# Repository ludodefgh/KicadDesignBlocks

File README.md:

# KicadDesignBlocks

Reusable KiCad circuit blocks: a schematic and its PCB layout, one self-contained
KiCad project per folder. Each project can be opened or shared on its own, for
example for an external review.

| Block | What it is | Status |
|---|---|---|
| [`TPS563201/`](TPS563201/) | Buck 5 V → 3.3 V / 1 A, TI TPS563201, 4 layers. Generated from the MultiSensors board (private repository) | layout done, not fabricated |
| [`TPS5430Buck/`](TPS5430Buck/) | Power input + buck based on the TI TPS5430: screw-terminal input, polyfuses (schematic note: "5/12/24V Power In") | earlier stand-alone project, history imported from the former `TPS5430Buck` repo |

## Conventions

- One folder per block, named after the main part, holding its own `.kicad_pro`.
- Symbols that are not in the standard KiCad libraries go in a project-local library
  (`sym/`, declared in the folder's `sym-lib-table`), so the project opens anywhere.
- `docs/` holds what a reviewer needs without KiCad: schematic PDF, layout image, and
  the sources the values came from.
- If a block is generated from another project, its README says so and names the
  script. Change it at the source and re-export.

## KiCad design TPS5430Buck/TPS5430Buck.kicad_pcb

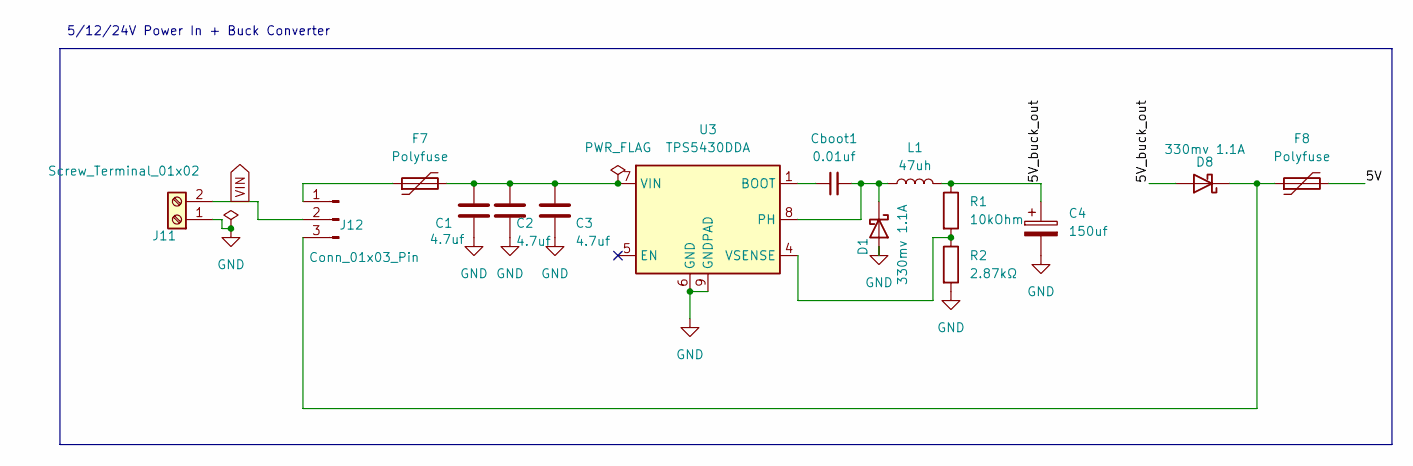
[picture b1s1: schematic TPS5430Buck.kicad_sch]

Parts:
C1, C2, C3: 4.7uf; C_1206_3216Metric; LCSC C29823
C4: 150uf; CP_EIA-7343-31_Kemet-D; LCSC C1953305
Cboot1: 0.01uf; R_0805_2012Metric; LCSC C1710
D1, D8: 330mv 1.1A; D_SMA; LCSC C8678
F7: Polyfuse; Fuse_1206_3216Metric; LCSC C7542958
F8: Polyfuse; Fuse_1206_3216Metric; LCSC C883127
J11: Screw_Terminal_01x02; TerminalBlock_Ningbo-Kagnex_HB9500M_1x02_P9.5mm; lcsc C601239
J12: Conn_01x03_Pin; PinHeader_1x03_P2.54mm_Vertical
L1: 47uh; L_7.3x7.3_H4.5; LCSC C168137
R1: 10kOhm; R_0201_0603Metric; LCSC C106225
R2: 2.87kΩ; R_0402_1005Metric; LCSC C334673
U3: TPS5430DDA; TI_SO-PowerPAD-8_ThermalVias; LCSC C9864

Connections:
/5V: F8.2
/5V_buck_out: C4.1, D8.2 (A), L1.2, R1.1
GND: C1.2, C2.2, C3.2, C4.2, D1.2 (A), J11.1, R2.2, U3.6 (GND), U3.9 (GNDPAD)
unnamed: Cboot1.2, D1.1 (K), L1.1, U3.8 (PH)
unnamed: D8.1 (K), F8.1, J12.3
unnamed: F7.1, J12.1
unnamed: Cboot1.1, U3.1 (BOOT)
unnamed: C1.1, C2.1, C3.1, F7.2, U3.7 (VIN)
unnamed: R1.2, R2.1, U3.4 (VSENSE)
VIN: J11.2, J12.2

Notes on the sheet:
5/12/24V Power In + Buck Converter

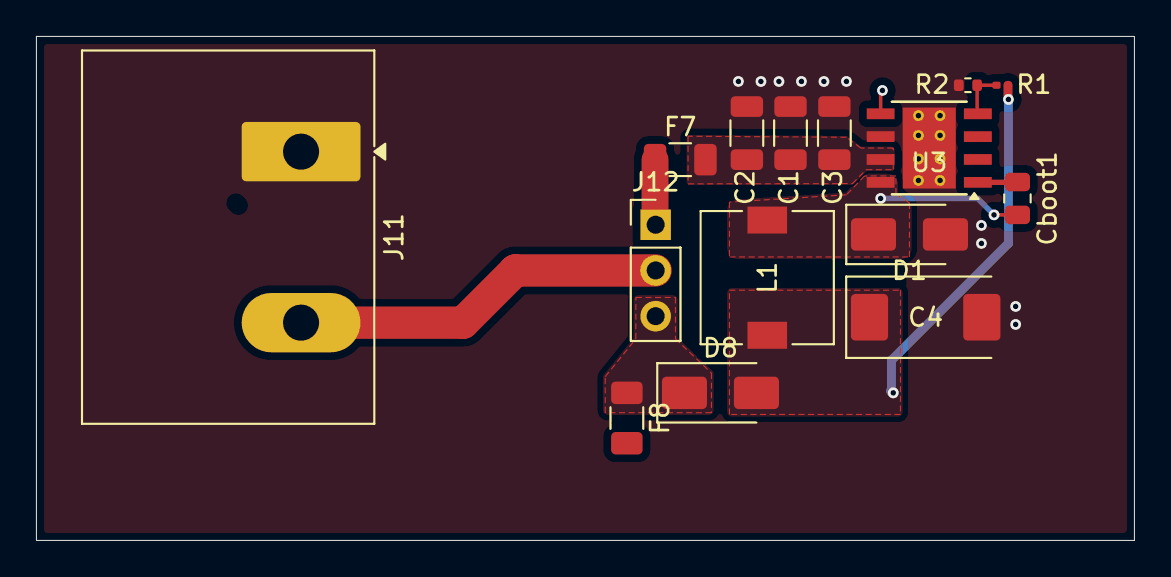
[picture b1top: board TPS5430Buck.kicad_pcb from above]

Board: 2 copper layers, 61.0 x 28.0 mm, 15 parts (0 on the bottom side), 9 nets.

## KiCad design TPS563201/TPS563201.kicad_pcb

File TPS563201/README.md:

# TPS563201 buck block: 5 V → 3.3 V / 1 A

A self-contained KiCad 10 project with just the TPS563201 and its passives, as laid
out in the MultiSensors sensor node (a private repository). It
exists so the power stage can be reviewed on its own, without the rest of the board.

| File | What it is |
|---|---|
| `TPS563201.kicad_pro` / `.kicad_sch` / `.kicad_pcb` | the project (open the `.kicad_pro`) |
| `docs/TPS563201-schematic.pdf` | schematic, readable without KiCad |
| `docs/TPS563201-layout.svg` | F.Cu, B.Cu, silkscreen and outline, readable without KiCad |
| `docs/webench/` | TI WEBENCH exports the part values came from (BOM CSV, layout images) |
| `sym/Block.kicad_sym` | project-local symbols, so the project opens on any machine |

## Operating point

| | Value |
|---|---|
| Input | 4.75–5.25 V, USB-C VBUS (the connector is outside this block) |
| Output | 3.32 V (0.768 V × (1 + 33.2 k / 10.0 k)) |
| Design current | 1 A (expected load: about 100 mA average, about 570 mA peak) |
| Switching frequency | 580 kHz (TPS563201, D-CAP2, Eco-mode at light load) |
| Main loads on 3.3 V | MCU radio bursts, SCD41 CO₂ sensor (asks for a low-noise supply) |

## Parts

| Ref | Part | Value | LCSC |
|---|---|---|---|
| U11 | TI TPS563201DDCR, SOT-23-6 | | C116592 |
| L1 | Sunlord SWPA4030S3R3MT, 4 × 4 × 3 mm | 3.3 µH, Isat 3.6 A, DCR 52 mΩ | C15269 |
| C5, C6 | Samsung CL21A106KAYNNNE, 0805 | 10 µF 25 V X5R (input) | C15850 |
| C7 | 0805 | 100 nF (input, high-frequency) | |
| C8, C9 | Samsung CL21A226MAQNNNE, 0805 | 22 µF 25 V X5R (output) | C45783 |
| C4 | Samsung CL05B104KO5NNNC, 0402 | 100 nF (bootstrap) | C1525 |
| R5, R6 | 0402, 1 % | 33.2 k / 10.0 k (feedback) | |

- **L1**: at 4.75–5.25 V in, the ripple is 0.52–0.64 A peak-to-peak, so the inductor
  peaks at about 1.3 A at 1 A out.
- **Output capacitors**: two 22 µF give about 29.6 µF at 3.3 V DC bias (Samsung
  DC-bias curve), inside TI's 20–68 µF range. The Samsung part is marked NRND; its
  replacement CL21A226MAYNNN (C602037) gives about 27.4 µF.
- **C7**: optional in TI's Table 7-2, kept because the TPS563201EVM-715 fits it (C1)
  and WEBENCH reserves a spot for it.

## Board and layout

- **4 layers: F.Cu / In1 = GND plane / In2 = +3.3 V plane / B.Cu.** The inner planes
  are cut to this block's outline. In the full board they cover the whole PCB.
- All parts are on the top side, for hot-plate assembly.
- The layout follows TI SLVSD90B §7.4 (fig. 7-18) and the TPS563201EVM-715 (SLVUAK7):
  - C7 sits across U11 pins 1 (GND) and 3 (VIN), at the same 1.9 mm pitch. The SW
    node leaves between its pads, under its body.
  - C5 and C6 sit right behind C7, on shared GND / +5 V copper areas.
  - L1 is above U11. The SW node is a small island: a copper area on F.Cu, plus a
    small area on B.Cu that crosses under the GND path through vias.
  - The input and output capacitors share one GND copper area that ties into U11
    pin 1.
  - The feedback divider sits on the quiet side of U11, away from L1 and SW.
- Design rules come from MultiSensors: 0.15 mm clearance, 0.4 mm minimum on power
  nets (`TPS563201.kicad_dru`).

## Where a review would help

1. **SW copper on B.Cu.** It faces the +3.3 V plane at about 0.2 mm. It is about
   5 mm², which estimates to about 1 pF onto a heavily decoupled plane. The
   alternative is to move it onto In2, cut into the 3.3 V plane.
2. **Bootstrap path.** C4 sits between L1 and U11 and picks up SW from L1's SW pad
   on F.Cu: about 1.3 mm of trace between the two pad edges, over the GND plane.
3. **Feedback sense.** R5 measures the output through a via into the +3.3 V plane,
   not through a dedicated trace from the output capacitors (TI rule 6). R6 returns
   to GND through its own via, not a Kelvin connection to U11 pin 1 (rule 7).
4. **No series resistor on the bootstrap capacitor.** The TI EVM fits a 0 Ω (R5
   there) so the SW edges can be slowed for EMC. There is none here.

## Status

Not fabricated, not measured. The schematic passes ERC (one warning: the +5V net has
both a power symbol and a label, as in the full board). The PCB passes DRC with 0
errors, 0 unconnected items and 0 schematic/PCB mismatches.

## Source

This project is **generated** from MultiSensors with
`kicad/_generators/export_tps563201_block.py <this folder>`. The script takes values,
footprints and MPN/LCSC fields from the MultiSensors schematic, and the layout from
the user's hand-drawn U11 group in the MultiSensors board. Change the block in
MultiSensors and re-export; edits made only here are lost at the next export.

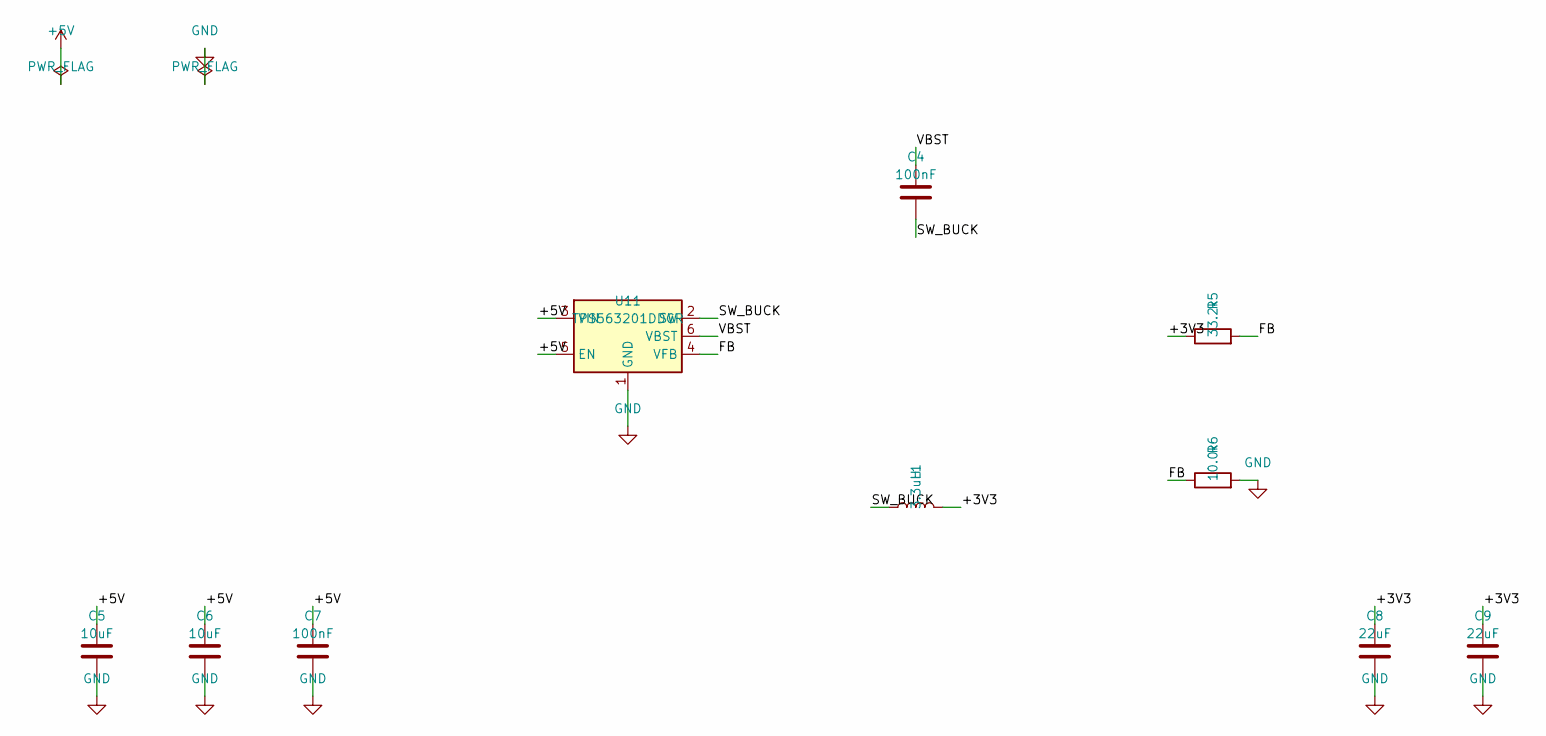
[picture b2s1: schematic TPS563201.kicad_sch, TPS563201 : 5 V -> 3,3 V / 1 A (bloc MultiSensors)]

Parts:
C4: 100nF; C_0402_1005Metric; MPN Samsung CL05B104KO5NNNC (100nF 16V X7R); LCSC C1525
C5, C6: 10uF; C_0805_2012Metric; MPN Samsung CL21A106KAYNNNE (10uF 25V X5R); LCSC C15850
C7: 100nF; C_0805_2012Metric
C8, C9: 22uF; C_0805_2012Metric; MPN Samsung CL21A226MAQNNNE (22uF 25V X5R); LCSC C45783
L1: 3.3uH; L_Sunlord_SWPA4030S; MPN Sunlord SWPA4030S3R3MT; LCSC C15269
R5: 33.2k; R_0402_1005Metric
R6: 10.0k; R_0402_1005Metric
U11: TPS563201DDCR; SOT-23-6

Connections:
+5V: C5.1, C6.1, C7.1, U11.3 (VIN), U11.5 (EN)
/+3V3: C8.1, C9.1, L1.2, R5.1
/FB: R5.2, R6.1, U11.4 (VFB)
/SW_BUCK: C4.2, L1.1, U11.2 (SW)
/VBST: C4.1, U11.6 (VBST)
GND: C5.2, C6.2, C7.2, C8.2, C9.2, R6.2, U11.1 (GND)

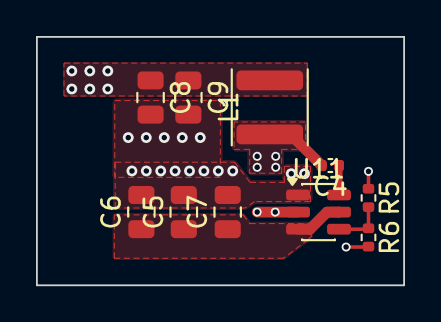
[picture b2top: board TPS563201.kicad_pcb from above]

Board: 4 copper layers, 20.4 x 13.8 mm, 10 parts (0 on the bottom side), 6 nets.
